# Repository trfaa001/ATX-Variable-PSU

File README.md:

# ATX-Variable-PSU
DIY variable power supply using an ATX PSU and buck converter.

## Features
---

* Voltage: 0-50V
* Amperage: 8A
* Repurposing ATX PSU
* Low-cost

## Parts list
---
| Qty | Component               | Notes                          | Link |
|-----|--------------------------|--------------------------------|------------------|
| 1   | ATX Power Supply                        | Corsair CV650                             | [Product page](https://www.corsair.com/us/en/p/psu/cp-9020211-na/cv-series-cv650-650-watt-80-plus-bronze-certified-psu-cp-9020211-na) |
| 1   | Buck Converter Module                   | XY5008E from Aliexpress                   | [Product page](https://www.aliexpress.com/item/1005005247897362.html) |
| 1   | Banana Plug Connectors                  | 1 red, 1 black                            | [Product page](https://www.aliexpress.com/item/1005006516519813.html) |
| 1   | XT90 Female Connector                   | High current output connector             | [Product page](https://www.aliexpress.com/item/1005007620266465.html) |
| 1   | XT90 Male Plug                          | High current plug                         | [Product page](https://www.aliexpress.com/item/1005008308472728.html) |
| 1   | 4mm Banana plug to alligator clip       | Standard test leads                       | [Product page](https://www.aliexpress.com/item/1005006537881871.html) |
| 1   | Enclosure                               | 3D printed (see Fusion file)              | [Mechanical (Fusion 360 + STL)](mechanical/)   |
| 1   | PCB                                     | Connecting the ATX 12V to a single line   | [PCB design (Kicad + exports)](hardware/kicad/)   |
| ~30 | Screws M3x10 mm                         | Connecting the parts togheter             | [Product page](https://www.aliexpress.com/item/32836902463.html) |
| —   | Wires, Heat Shrink, etc.                | For connections                           | — |

## Recommended 3d print settings
---
| Setting        | Value                    | Notes                          |
|----------------|--------------------------|--------------------------------|
| Layer Height   | maximum 0.22 mm            | Standard balance of speed/quality |
| Infill         | minimum 10%                | Higher infill for more strength |
| Perimeters     | 2-3                        | Improves wall strength          |
| Material       | PLA or PETG                | PETG for heat resistance        |
| Supports       | everywhere                 | Depends on model orientation    |
| Bed Adhesion   | Brim                       | If warping occurs               |

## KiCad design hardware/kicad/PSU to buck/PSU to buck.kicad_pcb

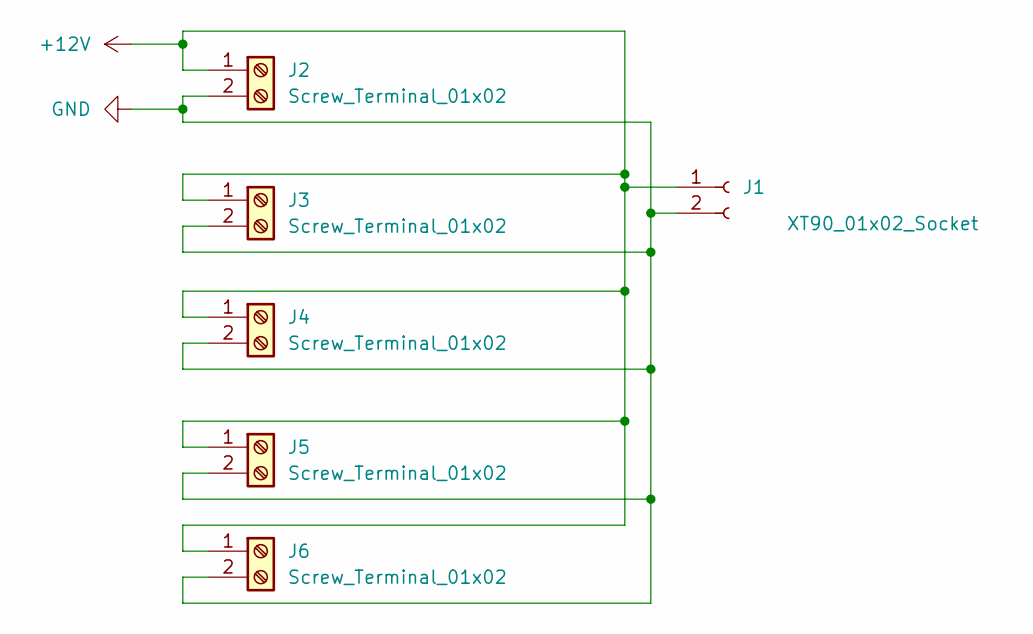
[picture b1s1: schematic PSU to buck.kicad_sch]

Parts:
J1: XT90_01x02_Socket; AMASS_XT90PW-M_1x02_P10.90mm_Horizontal
J2, J3, J4, J5, J6: Screw_Terminal_01x02; TerminalBlock_CUI_TB007-508-02_1x02_P5.08mm_Horizontal

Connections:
+12V: J1.1, J2.1, J3.1, J4.1, J5.1, J6.1
GND: J1.2, J2.2, J3.2, J4.2, J5.2, J6.2

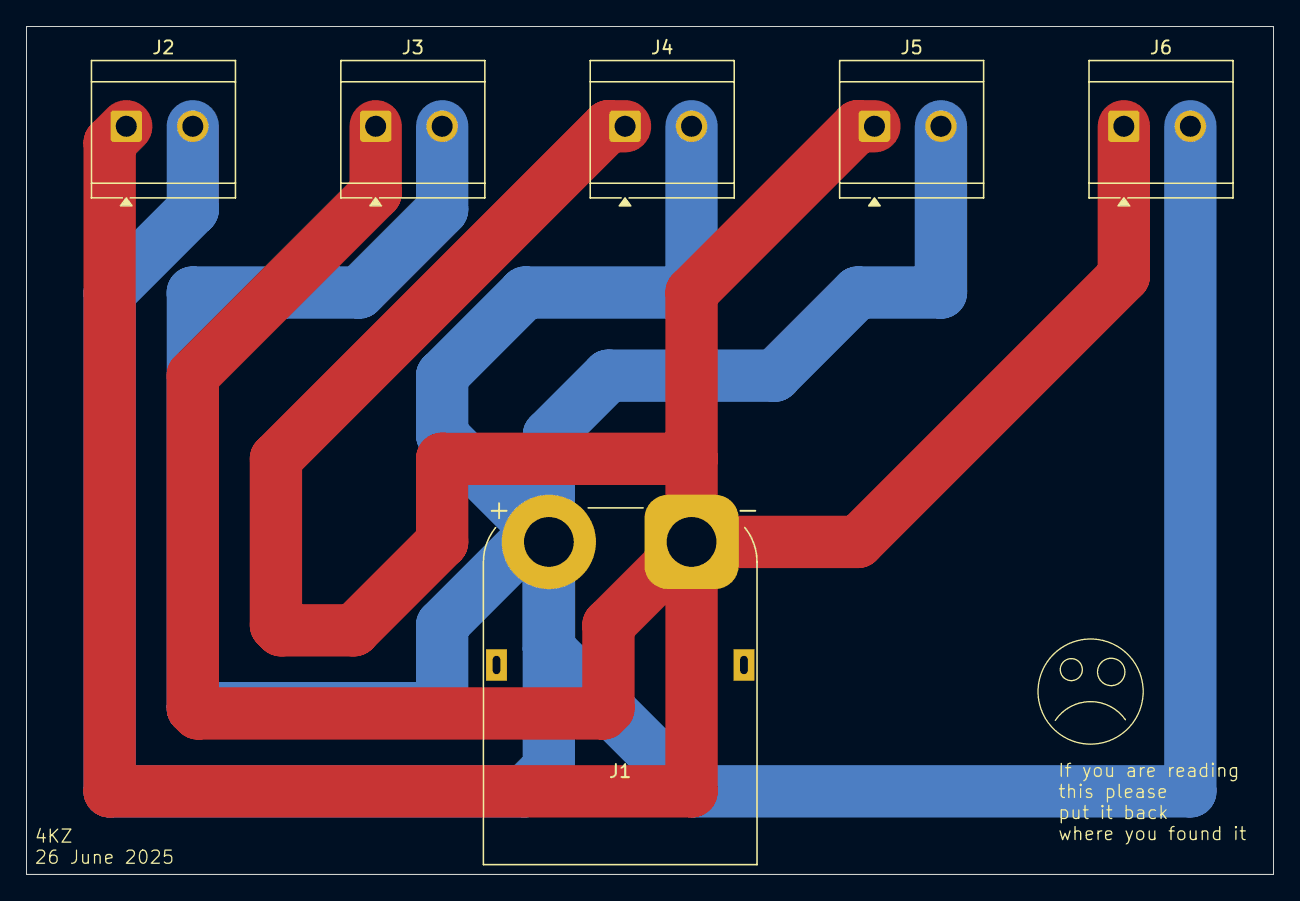
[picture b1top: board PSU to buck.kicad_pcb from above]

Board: 2 copper layers, 95.2 x 64.8 mm, 6 parts (0 on the bottom side), 2 nets.

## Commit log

2025-08-21 Initial
    First commit. Added files laying around.
2025-08-22 Update main README with features and parts list
    Expanded the README.md to include a project image, detailed features, and a comprehensive parts list with links. Removed redundant docs/README.md and hardware/part list.md files, and added the finish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
2025-08-22 Add KiCad PCB exports and update README
    Added generated drill, footprint, and Gerber files for the 'PSU to buck' PCB. Updated the project output paths in the KiCad project file. The README was updated to include PCB and 3D print settings. 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
2025-08-22 Update screw quantity and product link in README
    Changed the quantity of M3x10 mm screws from 1 to approximately 30 and updated the product link to a more relevant source in the parts list.
2025-08-30 Angled screw holes between front and back part
    This change fixes the issue where the screws couldnt be fully screwed in because of the lack of clearance.
